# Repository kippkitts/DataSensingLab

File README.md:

DataSensingLab
==============

Here, you’ll find files for the DataSensingLab.  Visit the DataSensingLab [website](http://datasensinglab.com/) for more information.

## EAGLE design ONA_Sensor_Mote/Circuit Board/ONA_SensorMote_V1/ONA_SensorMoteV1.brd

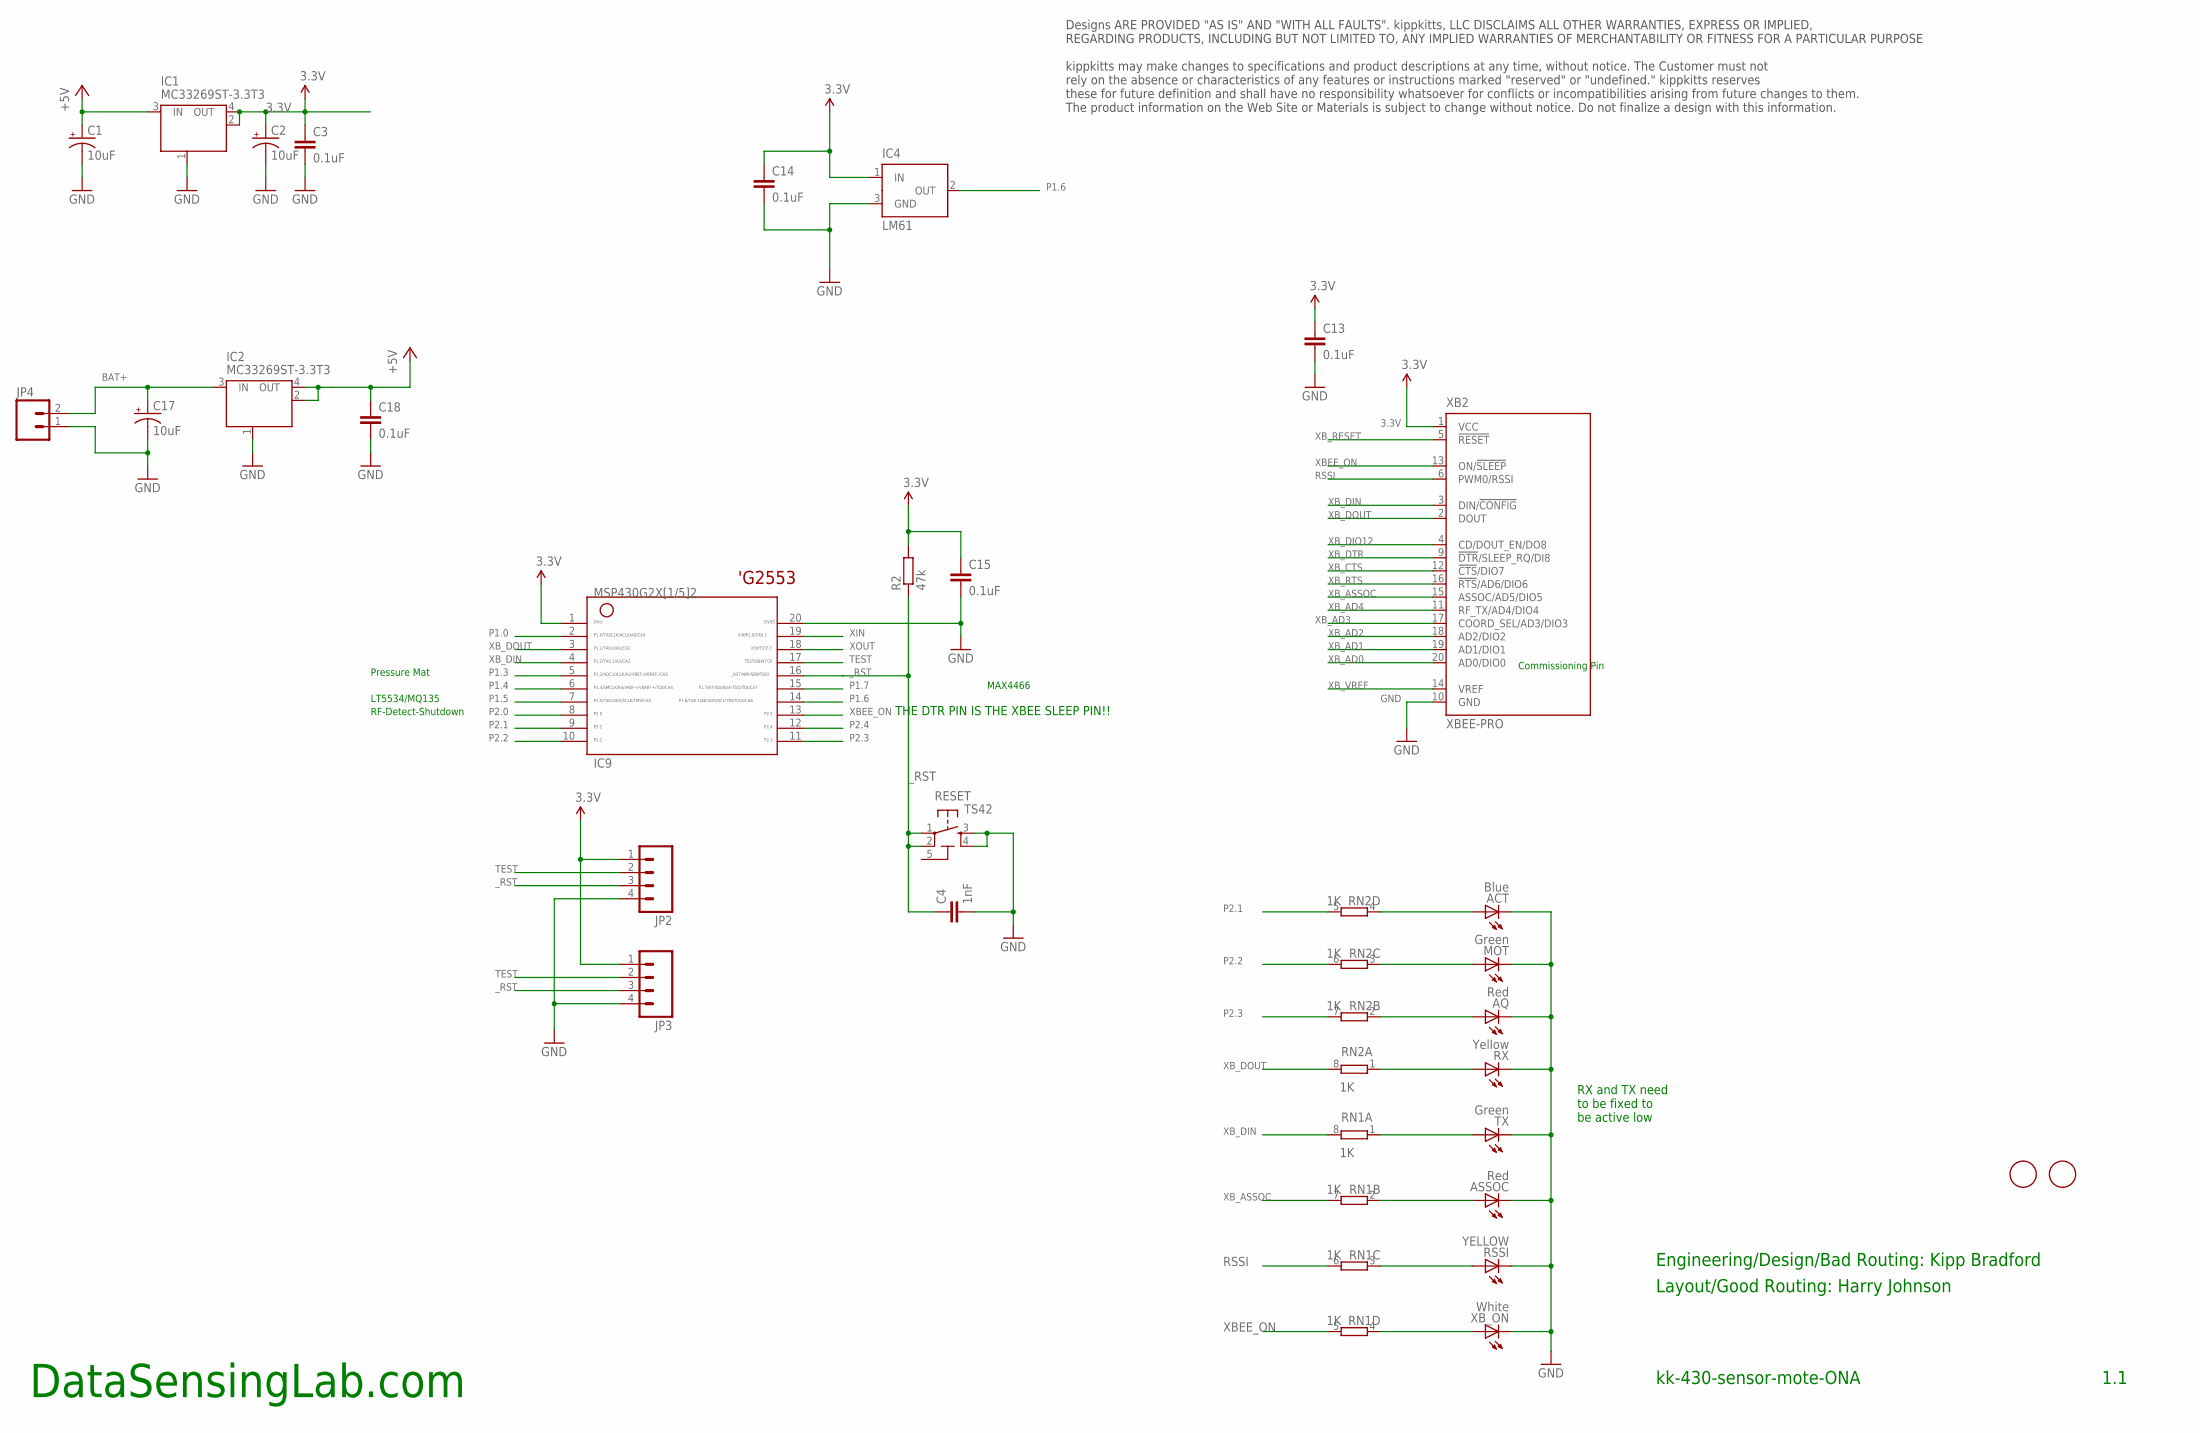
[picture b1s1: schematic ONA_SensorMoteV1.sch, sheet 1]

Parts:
A1, A2: FIDUCIALMOUNT; FIDUCIA-MOUNT
ACT: Blue; CHIP-LED0805
AQ: Red; CHIP-LED0805
ASSOC: Red; CHIP-LED0805
C1, C2, C17: 10uF; EIA3216
C3, C13, C14, C15, C18: 0.1uF; C0805K
C4: 1nF; C0805K
DISCLAIMER1: DISCLAIMERV1; DISCLAIMER
IC1, IC2: MC33269ST-3.3T3; SOT223
IC4: LM61; SOT23
IC9: G2X[1/5]2---PW20; PW20
JP2: M04SMD; 1X04-SMD
JP3: M04PTH; 1X04
JP4: M02; 1X02_LONGPADS
MOT: Green; CHIP-LED0805
R2: 47k; R0805
RESET: TS42
RN1, RN2: 1K; CAY16
RSSI: YELLOW; CHIP-LED0805
RX: Yellow; CHIP-LED0805
TX: Green; CHIP-LED0805
XB2: XBEE-PRO
XB_ON: White; CHIP-LED0805

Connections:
3.3V: C2.A (+), C3.1, C13.1, C14.1, C15.1, IC1.2 (OUT), IC1.4 (OUT), IC4.1 (IN), IC9.1, JP2.1, JP3.1, R2.2, XB2.1 (VCC); also elsewhere on the board
5-GND: RESET.5 (5-GND)
+5V: C1.A (+), C18.1, IC1.3 (IN), IC2.2 (OUT), IC2.4 (OUT); also elsewhere on the board
BAT+: C17.A (+), IC2.3 (IN), JP4.2
GND: ACT.C, AQ.C, ASSOC.C, C1.C (-), C2.C (-), C3.2, C4.2, C13.2, C14.2, C15.2, C17.C (-), C18.2, IC1.1 (GND/ADJ), IC2.1 (GND/ADJ), IC4.3 (GND), IC9.20, JP2.4, JP3.4, JP4.1, MOT.C, RESET.3, RESET.4, RSSI.C, RX.C, TX.C, XB2.10 (GND), XB_ON.C; also elsewhere on the board
unnamed: RN1.1, TX.A
unnamed: ASSOC.A, RN1.2 (1)
unnamed: ACT.A, RN2.4 (1)
unnamed: MOT.A, RN2.3 (1)
unnamed: RN1.3 (1), RSSI.A
unnamed: AQ.A, RN2.2 (1)
unnamed: RN2.1, RX.A
unnamed: RN1.4 (1), XB_ON.A
P1.0: IC9.2
P1.3: IC9.5; also elsewhere on the board
P1.4: IC9.6; also elsewhere on the board
P1.5: IC9.7; also elsewhere on the board
P1.6: IC4.2 (OUT), IC9.14
P1.7: IC9.15; also elsewhere on the board
P2.0: IC9.8; also elsewhere on the board
P2.1: IC9.9, RN2.5 (2)
P2.2: IC9.10, RN2.6 (2)
P2.3: IC9.11, RN2.7 (2); also elsewhere on the board
P2.4: IC9.12
RSSI: RN1.6 (2), XB2.6 (PWM0/RSSI)
TEST: IC9.17, JP2.2, JP3.2
XBEE_ON: IC9.13, RN1.5 (2), XB2.13 (ON/!SLEEP)
XB_AD0: XB2.20 (AD0/DIO0)
XB_AD1: XB2.19 (AD1/DIO1)
XB_AD2: XB2.18 (AD2/DIO2)
XB_AD3: XB2.17 (COORD_SEL/AD3/DIO3)
XB_AD4: XB2.11 (RF_TX/AD4/DIO4)
XB_ASSOC: RN1.7 (2), XB2.15 (ASSOC/AD5/DIO5)
XB_CTS: XB2.12 (!CTS!/DIO7)
XB_DIN: IC9.4, RN1.8 (2), XB2.3 (DIN/!CONFIG)
XB_DIO12: XB2.4 (CD/DOUT_EN/DO8)
XB_DOUT: IC9.3, RN2.8 (2), XB2.2 (DOUT)
XB_DTR: XB2.9 (!DTR!/SLEEP_RQ/DI8)
XB_RESET: XB2.5 (!RESET)
XB_RTS: XB2.16 (!RTS!/AD6/DIO6)
XB_VREF: XB2.14 (VREF)
XIN: IC9.19
XOUT: IC9.18
_RST: C4.1, IC9.16, JP2.3, JP3.3, R2.1, RESET.1, RESET.2

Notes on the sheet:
Commissioning Pin
MAX4466
LT5534/MQ135
Pressure Mat
RF-Detect-Shutdown
Engineering/Design/Bad Routing: Kipp Bradford
Layout/Good Routing: Harry Johnson
1.1
kk-430-sensor-mote-ONA
DataSensingLab.com
'G2553
RX and TX need to be fixed to be active low
THE DTR PIN IS THE XBEE SLEEP PIN!!

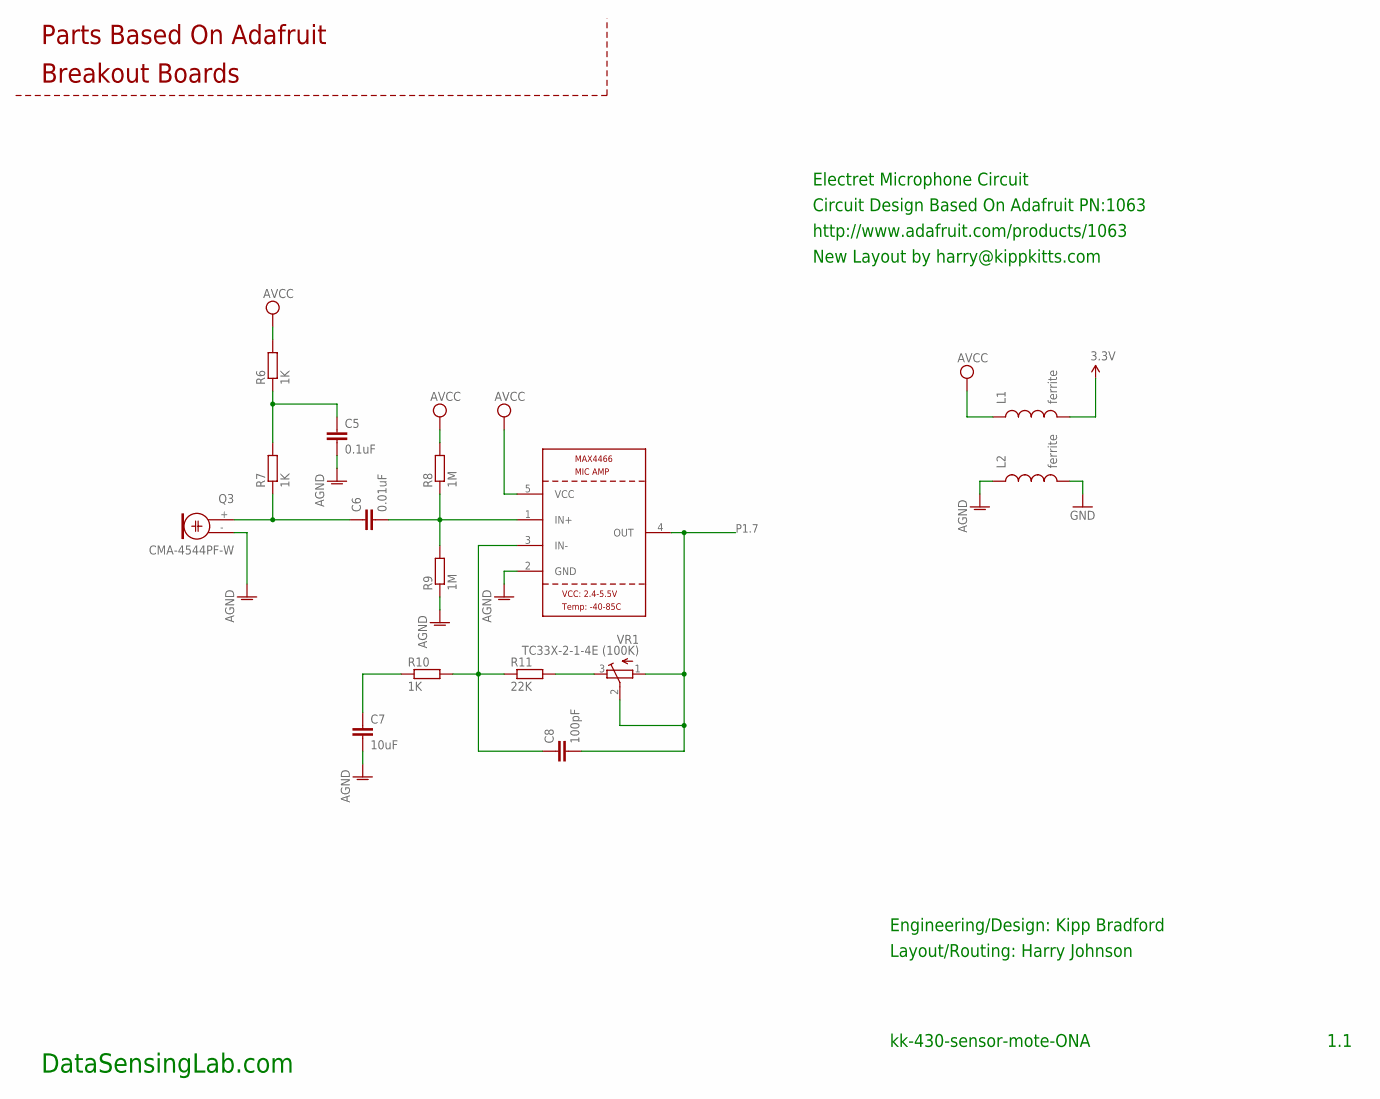
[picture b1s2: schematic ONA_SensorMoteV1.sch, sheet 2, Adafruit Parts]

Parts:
C5: 0.1uF; C0805K
C6: 0.01uF; C0805K
C7: 10uF; C0805K
C8: 100pF; C0805K
L1, L2: ferrite; 0603
Q3: CMA-4544PF-W; 9.7ELECTRET
R6, R7, R10: 1K; R0805
R8, R9: 1M; R0805
R11: 22K; R0805
U5: MAX4466SC70; SC70-5L
VR1: TC33X-2-1-4E (100K); TC33X

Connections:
3.3V: L1.2; also elsewhere on the board
AGND: C5.2, C7.2, L2.1, Q3.- (1), R9.1, U5.2 (GND)
GND: L2.2; also elsewhere on the board
unnamed: C6.1, Q3.+ (2), R7.1
unnamed: C6.2, R8.1, R9.2, U5.1 (IN+)
unnamed: C5.1, R6.1, R7.2
unnamed: C8.1, R10.2, R11.1, U5.3 (IN-)
unnamed: C7.1, R10.1
unnamed: R11.2, VR1.3 (E)
P1.7: C8.2, U5.4 (OUT), VR1.1 (A), VR1.2 (S); also elsewhere on the board
VCC: L1.1, R6.2, R8.2, U5.5 (VCC)

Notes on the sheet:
Parts Based On Adafruit
Breakout Boards
Circuit Design Based On Adafruit PN:1063
Electret Microphone Circuit
http://www.adafruit.com/products/1063
New Layout by harry@kippkitts.com
Engineering/Design: Kipp Bradford
Layout/Routing: Harry Johnson
1.1
kk-430-sensor-mote-ONA
DataSensingLab.com

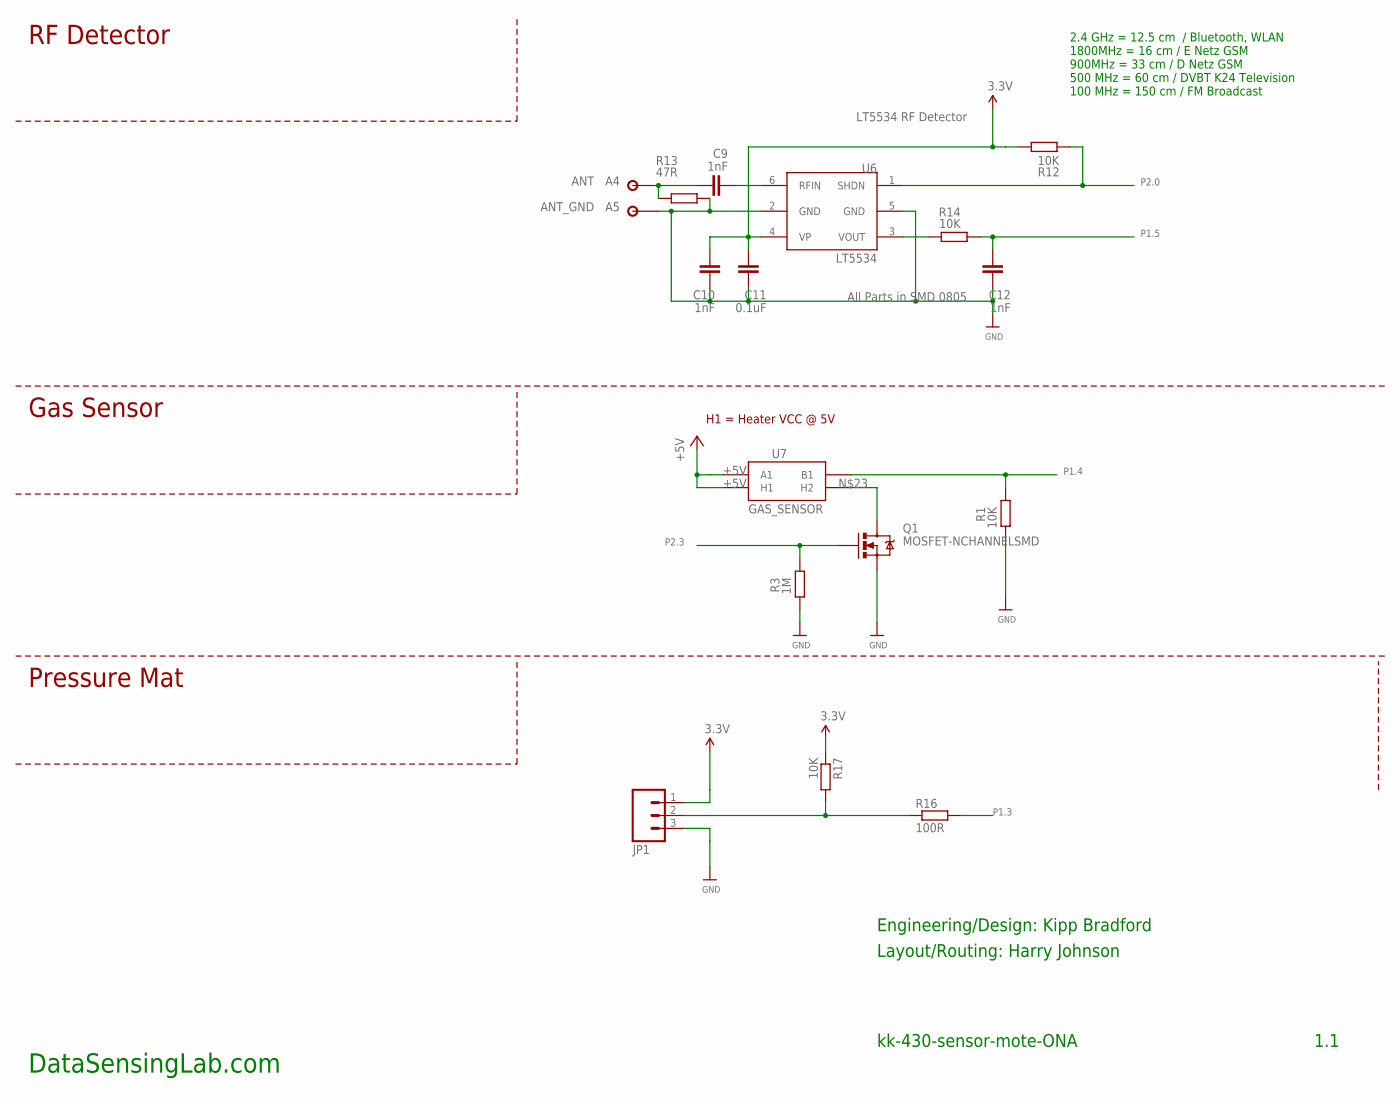
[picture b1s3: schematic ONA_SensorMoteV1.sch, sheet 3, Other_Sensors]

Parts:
A4: ANT; PAD146
A5: ANT_GND; PAD146
C9, C10, C12: 1nF; C0805K
C11: 0.1uF; C0805K
JP1: M03LOCK; 1X03_LOCK
Q1: MOSFET-NCHANNELSMD; SOT23-3
R1, R12, R14, R17: 10K; R0805
R3: 1M; R0805
R13: 47R; R0805
R16: 100R; R0805
U6: LT5534; SC70
U7: GAS_SENSOR; MQ-3

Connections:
3.3V: C10.2, C11.2, JP1.1, R12.2, R17.1, U6.4 (VP); also elsewhere on the board
+5V: U7.A1, U7.HA (H1); also elsewhere on the board
GND: A5.1, C10.1, C11.1, C12.1, JP1.3, Q1.2 (S), R1.1, R3.1, R13.2, U6.2 (GND), U6.5 (GND); also elsewhere on the board
unnamed: C9.1, U6.6 (RFIN)
unnamed: A4.1, C9.2, R13.1
unnamed: R14.1, U6.3 (VOUT)
unnamed: JP1.2, R16.1, R17.2
unnamed: Q1.3 (D), U7.HB (H2)
P1.3: R16.2; also elsewhere on the board
P1.4: R1.2, U7.B1; also elsewhere on the board
P1.5: C12.2, R14.2; also elsewhere on the board
P2.0: R12.1, U6.1 (SHDN); also elsewhere on the board
P2.3: Q1.1 (G), R3.2; also elsewhere on the board

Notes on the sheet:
All Parts in SMD 0805
LT5534 RF Detector
H1 = Heater VCC @ 5V
Pressure Mat
Gas Sensor
RF Detector
Engineering/Design: Kipp Bradford
Layout/Routing: Harry Johnson
1.1
kk-430-sensor-mote-ONA
DataSensingLab.com
2.4 GHz = 12.5 cm / Bluetooth, WLAN 1800MHz = 16 cm / E Netz GSM 900MHz = 33 cm / D Netz GSM 500 MHz = 60 cm / DVBT K24 Television 100 MHz = 150 cm / FM Broadcast

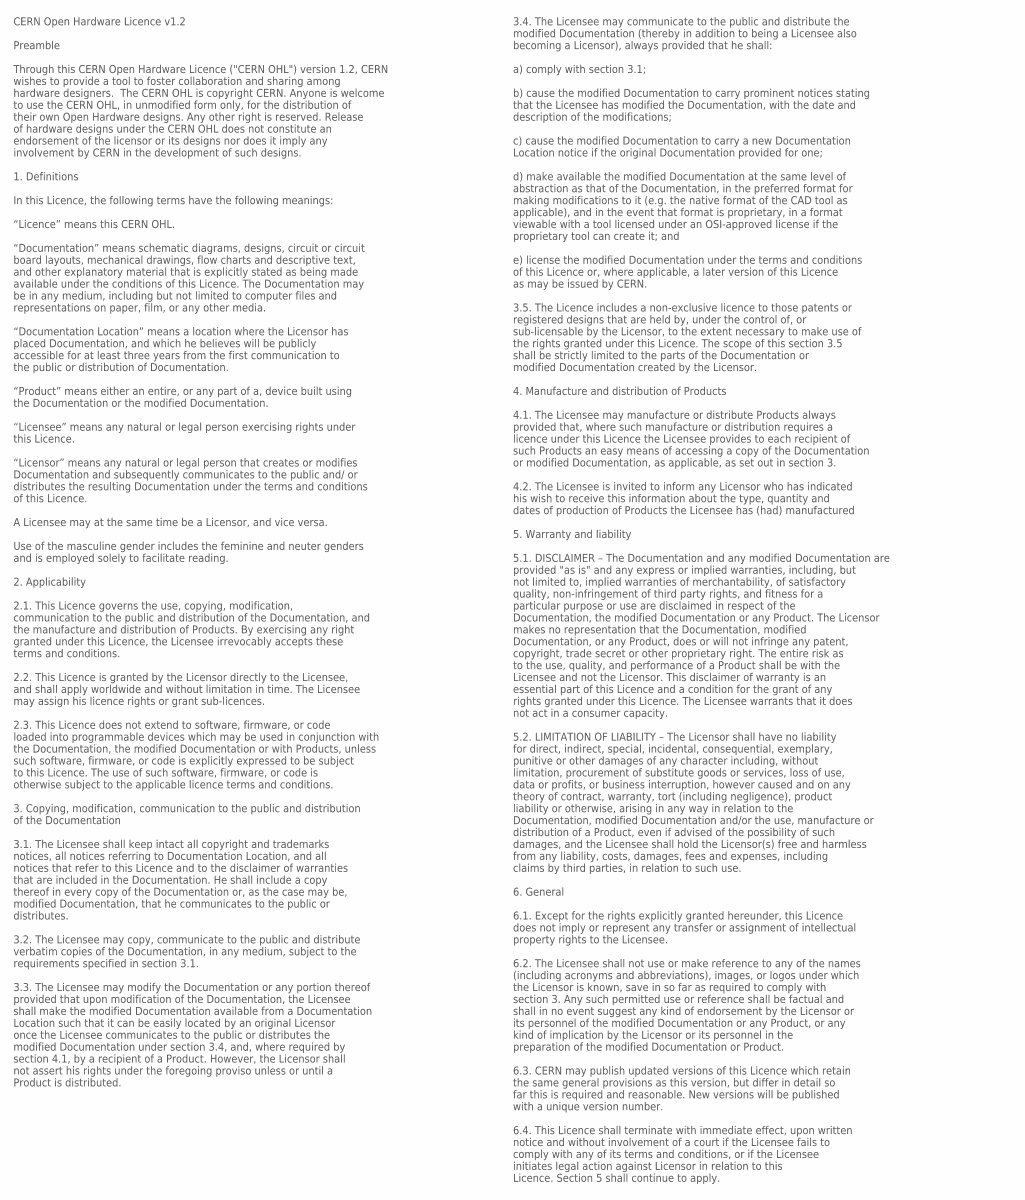
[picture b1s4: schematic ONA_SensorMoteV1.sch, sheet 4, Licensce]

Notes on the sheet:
CERN Open Hardware Licence v1.2 Preamble Through this CERN Open Hardware Licence ("CERN OHL") version 1.2, CERN wishes to provide a tool to foster collaboration and sharing among hardware designers. The CERN OHL is copyright CERN. Anyone is welcome to use the CERN OHL, in unmodified form only, for 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
3.4. The Licensee may communicate to the public and distribute the modified Documentation (thereby in addition to being a Licensee also becoming a Licensor), always provided that he shall: a) comply with section 3.1; b) cause the modified Documentation to carry prominent notices stating that the Li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

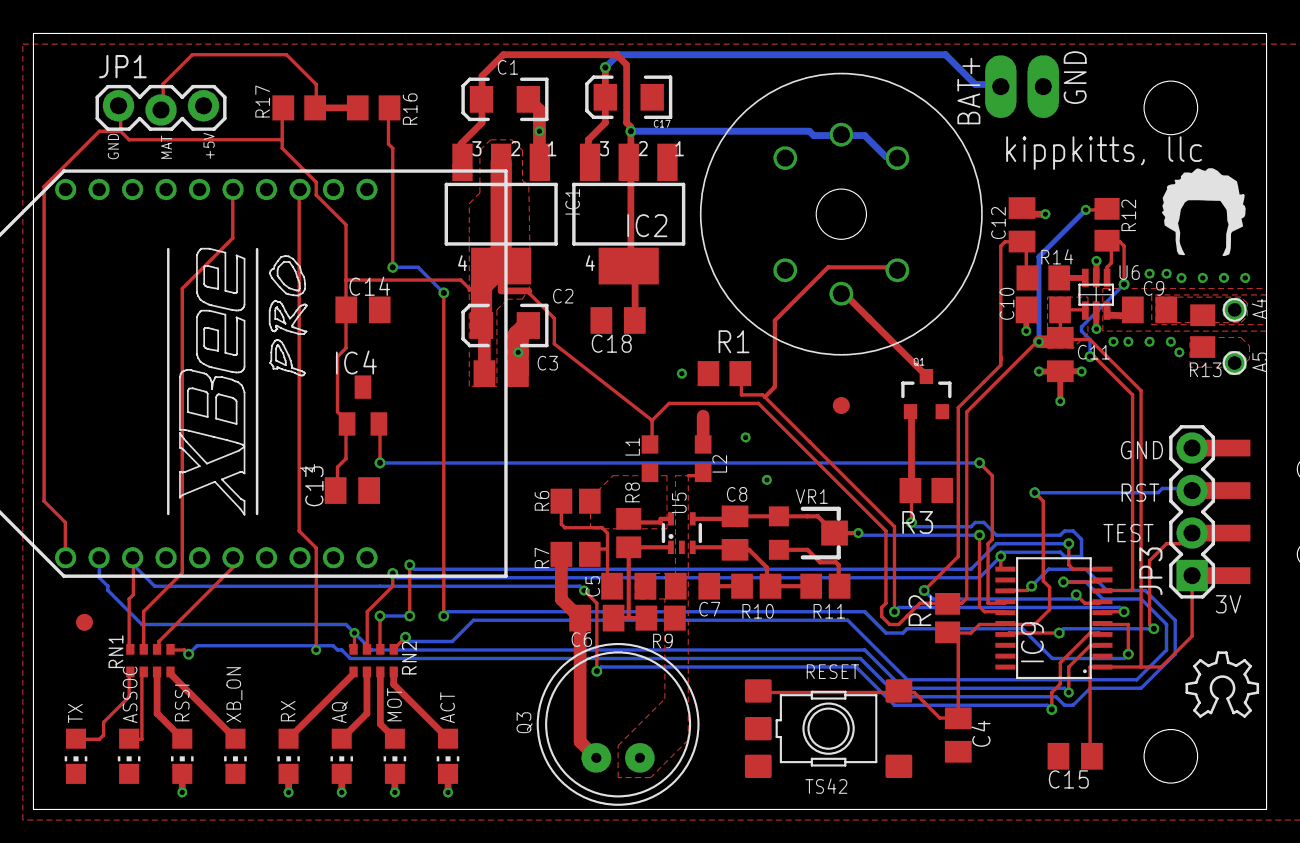
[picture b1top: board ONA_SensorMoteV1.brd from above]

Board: 2 copper layers, 73.7 x 46.4 mm, 66 parts (0 on the bottom side), 41 nets.

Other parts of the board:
U$3: OSHW_6X150_NOTEXT
U$5: TOP_DOCU_5MM

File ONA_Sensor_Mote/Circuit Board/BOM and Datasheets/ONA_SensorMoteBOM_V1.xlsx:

REF # | Qty | Value | Device | Package | Parts | Description | Digikey | MF | MPN
ONA-1 | 1 | BAT | BAT1 | 4AA | BAT1 | Battery Pack | SBH341AS-ND
ONA-2 | 1 |  | DNP | DNP | 6V In | Battery Pack Solder Pads
ONA-3 | 1 |  | M03LOCK | 1X03_LOCK | JP1 | 0.1" Pin Header for Motion Detector
ONA-4 | 1 |  | M04SMD | 1X04-SMD | JP2, JP3 optional | 0.1" Pin Header for Programming |  |  |  | 3M9502CT-ND
ONA-5 | 1 | 0.01uF | C-EUC0805K | C0805K | C6 | CAPACITOR, European symbol | 1276-1015-1-ND
ONA-6 | 7 | 0.1uF | C-EUC0805K | C0805K | C3, C5, C11, C13, C14, C15, C18 | CAPACITOR, European symbol | 399-1170-1-ND
ONA-7 | 1 | 100pF | C-EUC0805K | C0805K | C8 | CAPACITOR, European symbol | 399-1121-1-ND
ONA-8 | 1 | 10uF | C-EUC0805K | C0805K | C7 | Capacitor, Non-Polarized 0805 | 587-1300-1-ND
ONA-9 | 4 | 1nF | C-EUC0805K | C0805K | C4, C9, C10, C12 | CAPACITOR, European symbol | 399-1147-1-ND
ONA-10 | 3 | 10uF | CAP_POL1206 | EIA3216 | C1, C2, C17 | Capacitor Polarized Tantalum Supply Filter | 399-3687-1-ND
ONA-11 | 1 | 47R | R-EU_R0805 | R0805 | R13 | RESISTOR, European symbol | 311-47ARCT-ND
ONA-12 | 1 | 100R | R-EU_R0805 | R0805 | R16 | RESISTOR, European symbol | RHM100CLCT-ND
ONA-13 | 3 | 1K | R-EU_R0805 | R0805 | R6, R7, R10 | RESISTOR, European symbol | RHM1.0KCLCT-ND
ONA-14 | 4 | 10K | R-EU_R0805 | R0805 | R1, R12, R14, R17 | RESISTOR, European symbol | RMCF0805JT10K0CT-ND
ONA-15 | 1 | 22K | R-EU_R0805 | R0805 | R11 | RESISTOR, European symbol | 311-22KARCT-ND
ONA-16 | 1 | 47k | R-EU_R0805 | R0805 | R2 | RESISTOR, European symbol | RMCF0805JT47K0CT-ND
ONA-17 | 3 | 1M | R-EU_R0805 | R0805 | R3, R8, R9 | RESISTOR, European symbol | RHM1.00MCHCT-ND
ONA-18 | 2 | 1K | 4R-NCAY16 | CAY16 | RN1, RN2 | Array Chip Resistor | Y9102CT-ND
ONA-19 | 1 | TC33X-2-1-4E (100K) | TRIMPOTTC33X | TC33X | VR1 | SMT trimmer potentiometer part number TC33X | TC33X-104ECT-ND
ONA-20 | 2 | YELLOW | LEDCHIP-LED0805 | CHIP-LED0805 | RSSI, RX | LED | 475-2560-1-ND
ONA-21 | 1 | Blue | LEDCHIP-LED0805 | CHIP-LED0805 | ACT | LED | 160-1579-1-ND
ONA-22 | 1 | White | LEDCHIP-LED0805 | CHIP-LED0805 | XB_ON | LED | 160-1738-1-ND
ONA-23 | 2 | Red | LEDCHIP-LED0805 | CHIP-LED0805 | AQ, ASSOC | LED | 350-2039-1-ND
ONA-24 | 2 | Green | LEDCHIP-LED0805 | CHIP-LED0805 | MOT, TX | LED | 475-1410-1-ND
ONA-25 | 1 | CMA-4544PF-W | ELECTRET | 9.7ELECTRET | Q3 | Electret microphone | 102-1721-ND
ONA-26 | 1 | MSP430G2553 | MSP430G2553 | PW20 | IC9 | MSP430G2553 | 296-28430-1-ND
ONA-27 | 1 | GAS_SENSOR | GAS_SENSOR | MQ-3 | U7 | MQ-3 Gas Sensor. FP not tested. Part# |  | IN HAND
ONA-28 | 1 |  | MAX4466SC70 | SC70-5L | U5 | MAX4466 Mic Amp
ONA-29 | 1 | LM61 | LM61 | SOT23 | IC4 | Temperature Sensor | LM61BIM3X/NOPBCT-ND | TI | LM61
ONA-30 | 1 | LT5534 | LTC55 | SC70 | U6 | RF Signal Detector | LT5534ESC6#TRMPBFCT-ND
ONA-31 | 1 | MC33269ST-3.3T3 | MC33269ST-3.3T3 | SOT223 | IC1 | Adjustable Output Low Dropout Voltage Regulator 800 mA | MC33269ST-3.3T3GOSCT-ND
ONA-32 | 1 | MC33269ST-3.3T3 | MC33269ST-3.3T3 | SOT223 | IC2 | Adjustable Output Low Dropout Voltage Regulator 800 mA | NCP1117ST50T3GOSCT-ND
ONA-33 | 1 | MOSFET-NCHANNELSMD | MOSFET-NCHANNELSMD | SOT23-3 | Q1 | 1A Logic Level Mosfet | 785-1009-1-ND
ONA-34 | 1 | TS42 | TS42 | TS42 | RESET | TS42 | 679-2379-1-ND
ONA-35 | 1 | XBEE-SMT | XBEE-SMT | XBEE-SMT | SM34 | XB1 |  | XBee(TM)/XBee-PRO(TM) ZB SMT RF Modules.
ONA-36 | 2 | XBEE-HEADER | XBEE-PRO | XBEE-PRO | XB2 | XBee (TM) /XBee-PRO™ HEADER | S5751-10-ND |  | XBP24-AWI-001
ONA-37 | 2 | ferrite | INDUCTOR0603 | 603 | L1, L2 | Inductors | 445-1552-1-ND
 |  |  |  |  |  | Battery thing | SLPD-01-BLK-ND
 |  |  |  |  |  | LED | 897-1145-ND

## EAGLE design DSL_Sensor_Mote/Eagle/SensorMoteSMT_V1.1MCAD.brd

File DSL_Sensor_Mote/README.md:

DSL Sensor Mote
===============

##Hardware

The DSL Sensor Mote is a sensor shield for the Arduino Leonardo.  Included on this board are a motion detector, microphone, light sensor, air pressure sensor, and a temperature and humidity sensor.  There are two versions of the board - the [Sensor Mote Air Quality](http://kippkitts.gostorego.com/sensor-mote-aq.html), which also includes an MQ135 Air Quality Sensor, and the [Sensor Mote RF](http://kippkitts.gostorego.com/sensor-mote-rf.html), which can measure RF signal strength.  The shield also features an XBee 802.15.4 radio for wireless transmission of data.

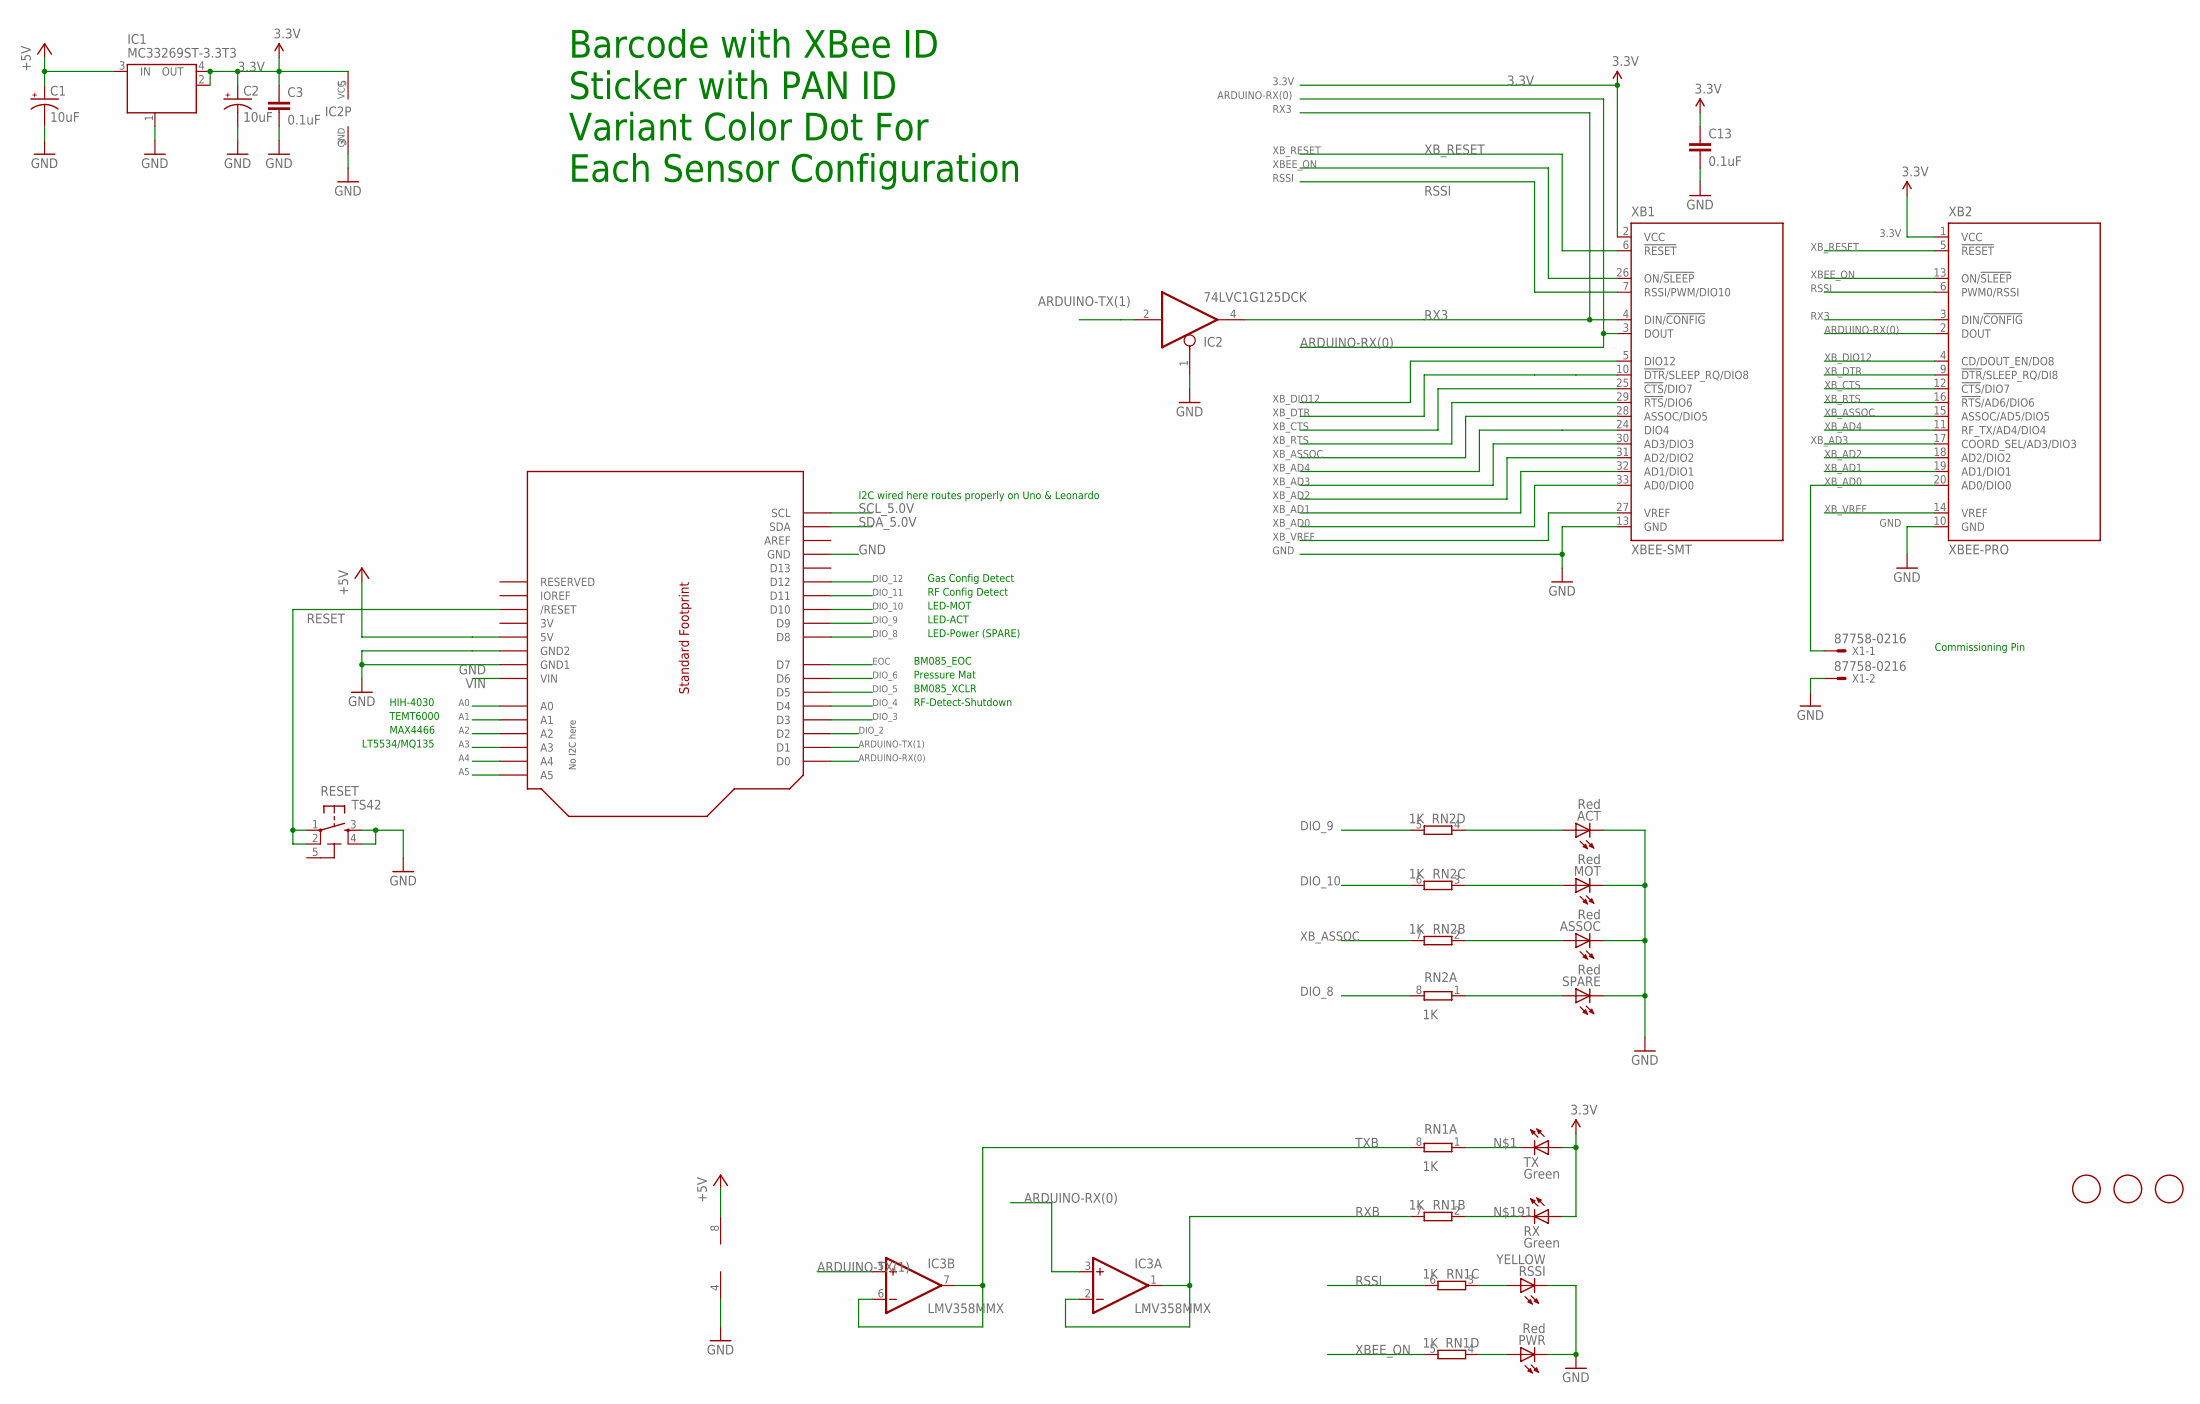
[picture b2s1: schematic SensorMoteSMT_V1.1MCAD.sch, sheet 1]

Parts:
A1, A2, A3: FIDUCIALMOUNT; FIDUCIA-MOUNT
ACT: Red; CHIP-LED0805
ASSOC: Red; CHIP-LED0805
C1, C2: 10uF; EIA3216
C3, C13: 0.1uF; C0805K
IC1: MC33269ST-3.3T3; SOT223
IC2: 74LVC1G125DCK; SC70-5
IC3: LMV358MMX; MSOP08
MOT: Red; CHIP-LED0805
PWR: Red; CHIP-LED0805
RESET: TS42
RN1, RN2: 1K; CAY16
RSSI: YELLOW; CHIP-LED0805
RX: Green; CHIP-LED0805
SPARE: Red; CHIP-LED0805
TX: Green; CHIP-LED0805
U1: ARDUINOR3; ARDUINOR3_EXTENDED
X1: 87758-0216
XB1: XBEE-SMT
XB2: XBEE-PRO

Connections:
3.3V: C2.A (+), C3.1, C13.1, IC1.2 (OUT), IC1.4 (OUT), IC2.5 (VCC), RX.A, TX.A, XB1.2 (VCC), XB2.1 (VCC); also elsewhere on the board
3V: U1.3V
5-GND: RESET.5 (5-GND)
+5V: C1.A (+), IC1.3 (IN), IC3.8 (V+), U1.5V; also elsewhere on the board
A0: U1.A0; also elsewhere on the board
A1: U1.A1; also elsewhere on the board
A2: U1.A2; also elsewhere on the board
A3: U1.A3; also elsewhere on the board
A4: U1.A4
A5: U1.A5
ARDUINO-RX(0): IC3.3 (+IN), U1.D0, XB1.3 (DOUT), XB2.2 (DOUT)
ARDUINO-TX(1): IC2.2 (I), IC3.5 (+IN), U1.D1
DIO_2: U1.D2
DIO_3: U1.D3
DIO_4: U1.D4; also elsewhere on the board
DIO_5: U1.D5; also elsewhere on the board
DIO_6: U1.D6; also elsewhere on the board
DIO_8: RN2.8 (2), U1.D8
DIO_9: RN2.5 (2), U1.D9
DIO_10: RN2.6 (2), U1.D10
DIO_11: U1.D11; also elsewhere on the board
DIO_12: U1.D12; also elsewhere on the board
EOC: U1.D7; also elsewhere on the board
GND: ACT.C, ASSOC.C, C1.C (-), C2.C (-), C3.2, C13.2, IC1.1 (GND/ADJ), IC2.1 (OE), IC2.3 (GND), IC3.4 (V-), MOT.C, PWR.C, RESET.3, RESET.4, RSSI.C, SPARE.C, U1.GND, U1.GND1, U1.GND2, X1.2, XB1.13 (GND), XB2.10 (GND); also elsewhere on the board
unnamed: RN1.1, TX.C
unnamed: ACT.A, RN2.4 (1)
unnamed: MOT.A, RN2.3 (1)
unnamed: RN1.3 (1), RSSI.A
unnamed: ASSOC.A, RN2.2 (1)
unnamed: RN2.1, SPARE.A
unnamed: PWR.A, RN1.4 (1)
unnamed: RN1.2 (1), RX.C
RESET: RESET.1, RESET.2, U1.RESET (/RESET)
RSSI: RN1.6 (2), XB1.7 (RSSI/PWM/DIO10), XB2.6 (PWM0/RSSI)
RX3: IC2.4 (O), XB1.4 (DIN/!CONFIG), XB2.3 (DIN/!CONFIG)
RXB: IC3.1 (OUT), IC3.2 (-IN), RN1.7 (2)
SCL_5.0V: U1.SCL; also elsewhere on the board
SDA_5.0V: U1.SDA; also elsewhere on the board
TXB: IC3.6 (-IN), IC3.7 (OUT), RN1.8 (2)
VIN: U1.VIN
XBEE_ON: RN1.5 (2), XB1.26 (ON/!SLEEP), XB2.13 (ON/!SLEEP)
XB_AD0: X1.1, XB1.33 (AD0/DIO0), XB2.20 (AD0/DIO0)
XB_AD1: XB1.32 (AD1/DIO1), XB2.19 (AD1/DIO1)
XB_AD2: XB1.31 (AD2/DIO2), XB2.18 (AD2/DIO2)
XB_AD3: XB1.30 (AD3/DIO3), XB2.17 (COORD_SEL/AD3/DIO3)
XB_AD4: XB1.24 (DIO4), XB2.11 (RF_TX/AD4/DIO4)
XB_ASSOC: RN2.7 (2), XB1.28 (ASSOC/DIO5), XB2.15 (ASSOC/AD5/DIO5)
XB_CTS: XB1.25 (!CTS!/DIO7), XB2.12 (!CTS!/DIO7)
XB_DIO12: XB1.5 (DIO12), XB2.4 (CD/DOUT_EN/DO8)
XB_DTR: XB1.10 (!DTR!/SLEEP_RQ/DIO8), XB2.9 (!DTR!/SLEEP_RQ/DI8)
XB_RESET: XB1.6 (!RESET), XB2.5 (!RESET)
XB_RTS: XB1.29 (!RTS!/DIO6), XB2.16 (!RTS!/AD6/DIO6)
XB_VREF: XB1.27 (VREF), XB2.14 (VREF)

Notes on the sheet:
Barcode with XBee ID
Each Sensor Configuration
Variant Color Dot For
Sticker with PAN ID
Commissioning Pin
HIH-4030
TEMT6000
MAX4466
LT5534/MQ135
I2C wired here routes properly on Uno & Leonardo
LED-MOT
LED-ACT
LED-Power (SPARE)
Pressure Mat
RF-Detect-Shutdown
Gas Config Detect
RF Config Detect
BM085_XCLR
BM085_EOC

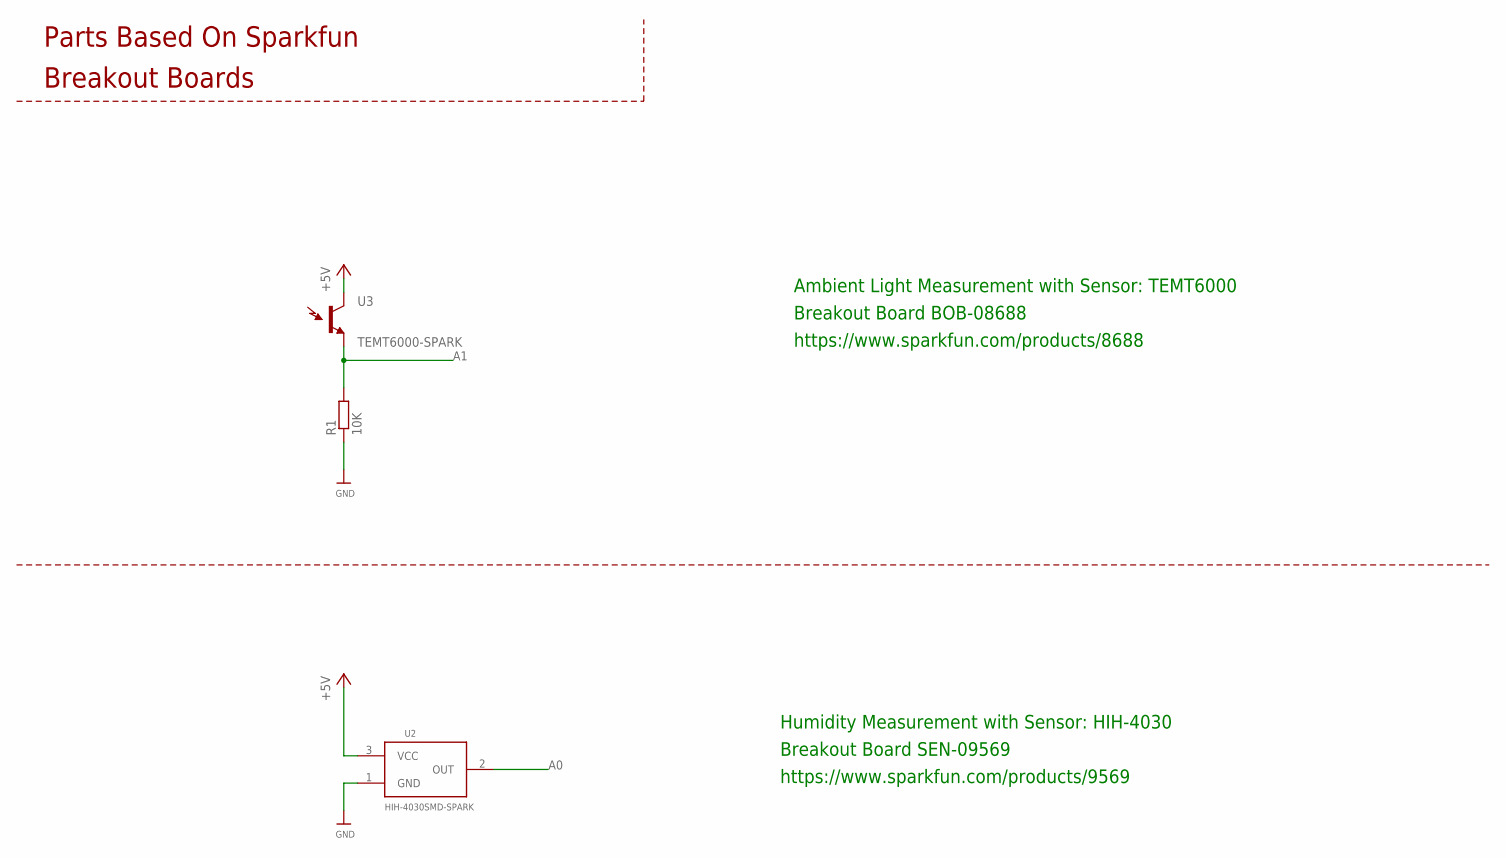
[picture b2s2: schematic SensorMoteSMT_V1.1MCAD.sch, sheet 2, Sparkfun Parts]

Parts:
R1: 10K; R0805
U2: HIH-4030SMD-SPARK; HIH-4030
U3: TEMT6000-SPARK; TEMT6000-SEN

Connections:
+5V: U2.3 (VCC), U3.COLLECTOR (C1); also elsewhere on the board
A0: U2.2 (OUT); also elsewhere on the board
A1: R1.2, U3.EMITTER (E1); also elsewhere on the board
GND: R1.1, U2.1 (GND); also elsewhere on the board

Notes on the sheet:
Parts Based On Sparkfun
Breakout Boards
Breakout Board SEN-09569
Humidity Measurement with Sensor: HIH-4030
https://www.sparkfun.com/products/9569
Breakout Board BOB-08688
Ambient Light Measurement with Sensor: TEMT6000
https://www.sparkfun.com/products/8688

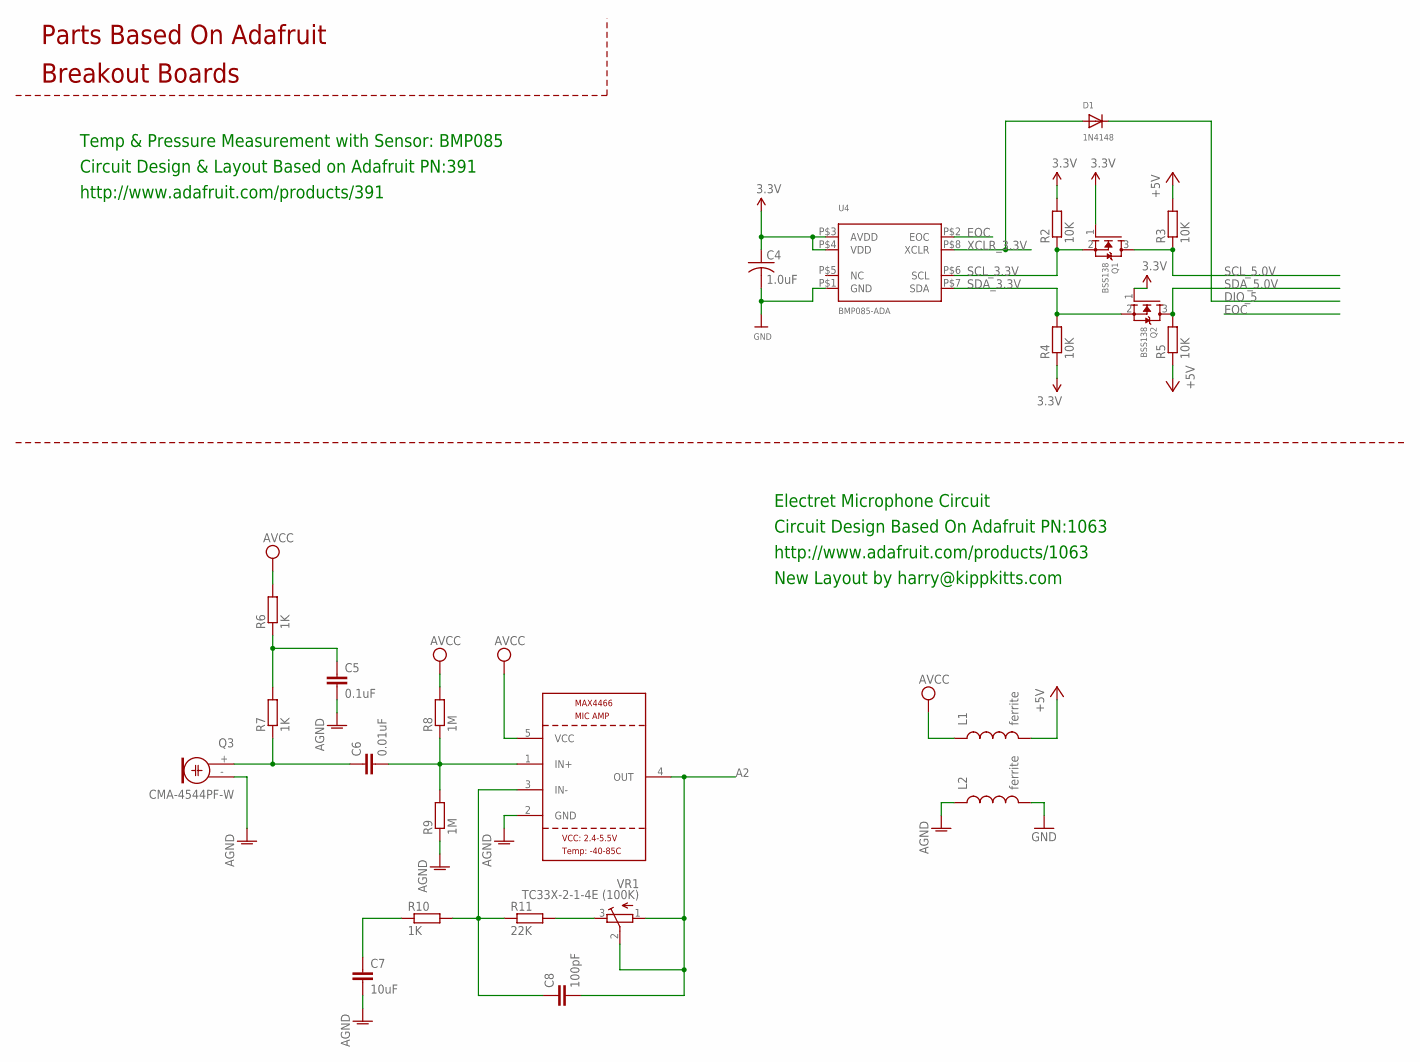
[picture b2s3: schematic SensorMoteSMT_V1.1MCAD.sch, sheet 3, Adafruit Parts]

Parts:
C4: 1.0uF; C0805K
C5: 0.1uF; C0805K
C6: 0.01uF; C0805K
C7: 10uF; C0805K
C8: 100pF; C0805K
D1: 1N4148; SOD-323F
L1, L2: ferrite; 0603
Q1, Q2: BSS138; SOT23
Q3: CMA-4544PF-W; 9.7ELECTRET
R2, R3, R4, R5: 10K; R0805
R6, R7, R10: 1K; R0805
R8, R9: 1M; R0805
R11: 22K; R0805
U4: BMP085-ADA; BMP085
U5: MAX4466SC70; SC70-5L
VR1: TC33X-2-1-4E (100K); TC33X

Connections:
3.3V: C4.1, Q1.1 (G), Q2.1 (G), R2.2, R4.1, U4.P$3 (AVDD), U4.P$4 (VDD); also elsewhere on the board
+5V: L1.2, R3.2, R5.1; also elsewhere on the board
A2: C8.2, U5.4 (OUT), VR1.1 (A), VR1.2 (S); also elsewhere on the board
AGND: C5.2, C7.2, L2.1, Q3.- (1), R9.1, U5.2 (GND)
DIO_5: D1.C; also elsewhere on the board
EOC: U4.P$2 (EOC); also elsewhere on the board
GND: C4.2, L2.2, U4.P$1 (GND); also elsewhere on the board
unnamed: C6.1, Q3.+ (2), R7.1
unnamed: C6.2, R8.1, R9.2, U5.1 (IN+)
unnamed: C5.1, R6.1, R7.2
unnamed: C8.1, R10.2, R11.1, U5.3 (IN-)
unnamed: C7.1, R10.1
unnamed: R11.2, VR1.3 (E)
SCL_3.3V: Q1.2 (S), R2.1, U4.P$6 (SCL)
SCL_5.0V: Q1.3 (D), R3.1; also elsewhere on the board
SDA_3.3V: Q2.2 (S), R4.2, U4.P$7 (SDA)
SDA_5.0V: Q2.3 (D), R5.2; also elsewhere on the board
VCC: L1.1, R6.2, R8.2, U5.5 (VCC)
XCLR_3.3V: D1.A, U4.P$8 (XCLR)

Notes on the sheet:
Circuit Design & Layout Based on Adafruit PN:391
Parts Based On Adafruit
Breakout Boards
Temp & Pressure Measurement with Sensor: BMP085
http://www.adafruit.com/products/391
Circuit Design Based On Adafruit PN:1063
Electret Microphone Circuit
http://www.adafruit.com/products/1063
New Layout by harry@kippkitts.com

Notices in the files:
ONA_Sensor_Mote/Circuit Board/ONA_SensorMote_V1/ONA_SensorMoteV1.sch:
to use the CERN OHL, in unmodified form only, for the distribution of
their own Open Hardware designs. Any other right is reserved. Release
of hardware designs under the CERN OHL does not constitute an
endorsement of the licensor or its designs nor does it imply any
available under the conditions of this Licence. The Documentation may
granted under this Licence, the Licensee irrevocably accepts these
viewable with a tool licensed under an OSI-approved license if the
proprietary tool can create it; and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
